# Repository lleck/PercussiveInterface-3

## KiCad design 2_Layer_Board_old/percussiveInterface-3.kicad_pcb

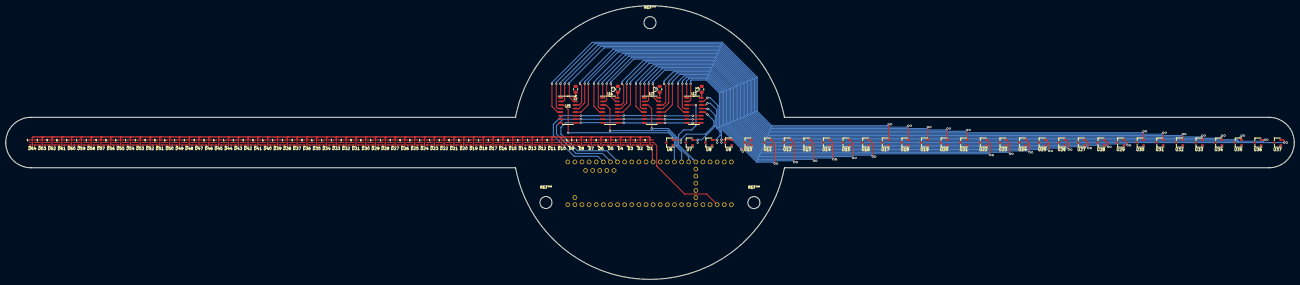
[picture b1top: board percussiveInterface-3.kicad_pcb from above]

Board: 2 copper layers, 460.0 x 97.7 mm, 105 parts (1 on the bottom side), 137 nets.

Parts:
C1, C2, C3, C4: 0.1µF; C_0805_2012Metric_Pad1.18x1.45mm_HandSolder
D1, D2, D3, D4, D5, D6, D7, D8, D9, D10, D11, D12, D13, D14, D15, D16, D17, D18, D19, D20, D21, D22, D23, D24, D25, D26, D27, D28, D29, D30, D31, D32, D33, D34, D35, D36, D37, D38, D39, D40, D41, D42, D43, D44, D45, D46, D47, D48, D49, D50, D51, D52, D53, D54, D55, D56, D57, D58, D59, D60, D61, D62, D63, D64: APA102-2020; LED-APA102-2020
U1: Teensy4.1; TEENSY41
U2, U3, U4, U5: 74HCT4051; SO-16_3.9x9.9mm_P1.27mm
U6, U7, U8, U9, U10, U11, U12, U13, U14, U15, U16, U17, U18, U19, U20, U21, U22, U23, U24, U25, U26, U27, U28, U29, U30, U31, U32, U33, U34, U35, U36, U37: SS39ET; SOT-23W

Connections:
+5V: C1.1, C2.1, C3.1, C4.1, D1.1 (VDD), D2.1 (VDD), D3.1 (VDD), D4.1 (VDD), D5.1 (VDD), D6.1 (VDD), D7.1 (VDD), D8.1 (VDD), D9.1 (VDD), D10.1 (VDD), D11.1 (VDD), D12.1 (VDD), D13.1 (VDD), D14.1 (VDD), D15.1 (VDD), D16.1 (VDD), D17.1 (VDD), D18.1 (VDD), D19.1 (VDD), D20.1 (VDD), D21.1 (VDD), D22.1 (VDD), D23.1 (VDD), D24.1 (VDD), D25.1 (VDD), D26.1 (VDD), D27.1 (VDD), D28.1 (VDD), D29.1 (VDD), D30.1 (VDD), D31.1 (VDD), D32.1 (VDD), D33.1 (VDD), D34.1 (VDD), D35.1 (VDD), D36.1 (VDD), D37.1 (VDD), D38.1 (VDD), D39.1 (VDD), D40.1 (VDD), D41.1 (VDD), D42.1 (VDD), D43.1 (VDD), D44.1 (VDD), D45.1 (VDD), D46.1 (VDD), D47.1 (VDD), D48.1 (VDD), D49.1 (VDD), D50.1 (VDD), D51.1 (VDD), D52.1 (VDD), D53.1 (VDD), D54.1 (VDD), D55.1 (VDD), D56.1 (VDD), D57.1 (VDD), D58.1 (VDD), D59.1 (VDD), D60.1 (VDD), D61.1 (VDD), D62.1 (VDD), D63.1 (VDD), D64.1 (VDD), U1.48 (VIN), U2.16 (VCC), U3.16 (VCC), U4.16 (VCC), U5.16 (VCC), U6.1 (VCC), U7.1 (VCC), U8.1 (VCC), U9.1 (VCC), U10.1 (VCC), U11.1 (VCC), U12.1 (VCC), U13.1 (VCC), U14.1 (VCC), U15.1 (VCC), U16.1 (VCC), U17.1 (VCC), U18.1 (VCC), U19.1 (VCC), U20.1 (VCC), U21.1 (VCC), U22.1 (VCC), U23.1 (VCC), U24.1 (VCC), U25.1 (VCC), U26.1 (VCC), U27.1 (VCC), U28.1 (VCC), U29.1 (VCC), U30.1 (VCC), U31.1 (VCC), U32.1 (VCC), U33.1 (VCC), U34.1 (VCC), U35.1 (VCC), U36.1 (VCC), U37.1 (VCC)
GND: C1.2, C2.2, C3.2, C4.2, D1.6 (GND), D2.6 (GND), D3.6 (GND), D4.6 (GND), D5.6 (GND), D6.6 (GND), D7.6 (GND), D8.6 (GND), D9.6 (GND), D10.6 (GND), D11.6 (GND), D12.6 (GND), D13.6 (GND), D14.6 (GND), D15.6 (GND), D16.6 (GND), D17.6 (GND), D18.6 (GND), D19.6 (GND), D20.6 (GND), D21.6 (GND), D22.6 (GND), D23.6 (GND), D24.6 (GND), D25.6 (GND), D26.6 (GND), D27.6 (GND), D28.6 (GND), D29.6 (GND), D30.6 (GND), D31.6 (GND), D32.6 (GND), D33.6 (GND), D34.6 (GND), D35.6 (GND), D36.6 (GND), D37.6 (GND), D38.6 (GND), D39.6 (GND), D40.6 (GND), D41.6 (GND), D42.6 (GND), D43.6 (GND), D44.6 (GND), D45.6 (GND), D46.6 (GND), D47.6 (GND), D48.6 (GND), D49.6 (GND), D50.6 (GND), D51.6 (GND), D52.6 (GND), D53.6 (GND), D54.6 (GND), D55.6 (GND), D56.6 (GND), D57.6 (GND), D58.6 (GND), D59.6 (GND), D60.6 (GND), D61.6 (GND), D62.6 (GND), D63.6 (GND), D64.6 (GND), U1.1 (GND), U1.34 (GND), U1.52 (GND), U2.6 (~E), U2.7 (VEE), U2.8 (GND), U3.6 (~E), U3.7 (VEE), U3.8 (GND), U4.6 (~E), U4.7 (VEE), U4.8 (GND), U5.6 (~E), U5.7 (VEE), U5.8 (GND), U6.3 (GND), U7.3 (GND), U8.3 (GND), U9.3 (GND), U10.3 (GND), U11.3 (GND), U12.3 (GND), U13.3 (GND), U14.3 (GND), U15.3 (GND), U16.3 (GND), U17.3 (GND), U18.3 (GND), U19.3 (GND), U20.3 (GND), U21.3 (GND), U22.3 (GND), U23.3 (GND), U24.3 (GND), U25.3 (GND), U26.3 (GND), U27.3 (GND), U28.3 (GND), U29.3 (GND), U30.3 (GND), U31.3 (GND), U32.3 (GND), U33.3 (GND), U34.3 (GND), U35.3 (GND), U36.3 (GND), U37.3 (GND)
unnamed: D1.2 (CKO), D2.5 (CKI)
unnamed: D1.3 (SDO), D2.4 (SDI)
unnamed: D1.4 (SDI), U1.11 (9_OUT1C)
unnamed: D1.5 (CKI), U1.35 (13_SCK_LED)
unnamed: D2.2 (CKO), D3.5 (CKI)
unnamed: D2.3 (SDO), D3.4 (SDI)
unnamed: D3.2 (CKO), D4.5 (CKI)
unnamed: D3.3 (SDO), D4.4 (SDI)
unnamed: D4.2 (CKO), D5.5 (CKI)
unnamed: D4.3 (SDO), D5.4 (SDI)
unnamed: D5.2 (CKO), D6.5 (CKI)
unnamed: D5.3 (SDO), D6.4 (SDI)
unnamed: D6.2 (CKO), D7.5 (CKI)
unnamed: D6.3 (SDO), D7.4 (SDI)
unnamed: D7.2 (CKO), D8.5 (CKI)
unnamed: D7.3 (SDO), D8.4 (SDI)
unnamed: D8.2 (CKO), D9.5 (CKI)
unnamed: D8.3 (SDO), D9.4 (SDI)
unnamed: D10.2 (CKO), D11.5 (CKI)
unnamed: D10.3 (SDO), D11.4 (SDI)
unnamed: D9.3 (SDO), D10.4 (SDI)
unnamed: D9.2 (CKO), D10.5 (CKI)
unnamed: D11.2 (CKO), D12.5 (CKI)
unnamed: D11.3 (SDO), D12.4 (SDI)
unnamed: D12.2 (CKO), D13.5 (CKI)
unnamed: D12.3 (SDO), D13.4 (SDI)
unnamed: D13.2 (CKO), D14.5 (CKI)
unnamed: D13.3 (SDO), D14.4 (SDI)
unnamed: D14.2 (CKO), D15.5 (CKI)
unnamed: D14.3 (SDO), D15.4 (SDI)
unnamed: D15.2 (CKO), D16.5 (CKI)
unnamed: D15.3 (SDO), D16.4 (SDI)
unnamed: D16.2 (CKO), D17.5 (CKI)
unnamed: D16.3 (SDO), D17.4 (SDI)
unnamed: D17.2 (CKO), D18.5 (CKI)
unnamed: D17.3 (SDO), D18.4 (SDI)
unnamed: D18.2 (CKO), D19.5 (CKI)
unnamed: D18.3 (SDO), D19.4 (SDI)
unnamed: D19.2 (CKO), D20.5 (CKI)
unnamed: D19.3 (SDO), D20.4 (SDI)
unnamed: D20.2 (CKO), D21.5 (CKI)
unnamed: D20.3 (SDO), D21.4 (SDI)
unnamed: D21.2 (CKO), D22.5 (CKI)
unnamed: D21.3 (SDO), D22.4 (SDI)
unnamed: D22.2 (CKO), D23.5 (CKI)
unnamed: D22.3 (SDO), D23.4 (SDI)
unnamed: D23.2 (CKO), D24.5 (CKI)
unnamed: D23.3 (SDO), D24.4 (SDI)
unnamed: D24.2 (CKO), D25.5 (CKI)
unnamed: D24.3 (SDO), D25.4 (SDI)
unnamed: D25.2 (CKO), D26.5 (CKI)
unnamed: D25.3 (SDO), D26.4 (SDI)
unnamed: D26.2 (CKO), D27.5 (CKI)
unnamed: D26.3 (SDO), D27.4 (SDI)
unnamed: D27.2 (CKO), D28.5 (CKI)
unnamed: D27.3 (SDO), D28.4 (SDI)
unnamed: D28.2 (CKO), D29.5 (CKI)
unnamed: D28.3 (SDO), D29.4 (SDI)
unnamed: D29.2 (CKO), D30.5 (CKI)
unnamed: D29.3 (SDO), D30.4 (SDI)
unnamed: D30.2 (CKO), D31.5 (CKI)
unnamed: D30.3 (SDO), D31.4 (SDI)
unnamed: D31.2 (CKO), D32.5 (CKI)
unnamed: D31.3 (SDO), D32.4 (SDI)
unnamed: D32.2 (CKO), D33.5 (CKI)
unnamed: D32.3 (SDO), D33.4 (SDI)
unnamed: D33.2 (CKO), D34.5 (CKI)
unnamed: D33.3 (SDO), D34.4 (SDI)
unnamed: D34.2 (CKO), D35.5 (CKI)
unnamed: D34.3 (SDO), D35.4 (SDI)
unnamed: D35.2 (CKO), D36.5 (CKI)
unnamed: D35.3 (SDO), D36.4 (SDI)
unnamed: D36.2 (CKO), D37.5 (CKI)
unnamed: D36.3 (SDO), D37.4 (SDI)
unnamed: D37.2 (CKO), D38.5 (CKI)
unnamed: D37.3 (SDO), D38.4 (SDI)
unnamed: D38.2 (CKO), D39.5 (CKI)
unnamed: D38.3 (SDO), D39.4 (SDI)
unnamed: D39.2 (CKO), D40.5 (CKI)
unnamed: D39.3 (SDO), D40.4 (SDI)
unnamed: D40.2 (CKO), D41.5 (CKI)
unnamed: D40.3 (SDO), D41.4 (SDI)
unnamed: D41.2 (CKO), D42.5 (CKI)
unnamed: D41.3 (SDO), D42.4 (SDI)
unnamed: D42.2 (CKO), D43.5 (CKI)
unnamed: D42.3 (SDO), D43.4 (SDI)
unnamed: D43.2 (CKO), D44.5 (CKI)
unnamed: D43.3 (SDO), D44.4 (SDI)
unnamed: D44.2 (CKO), D45.5 (CKI)
unnamed: D44.3 (SDO), D45.4 (SDI)
unnamed: D45.2 (CKO), D46.5 (CKI)
unnamed: D45.3 (SDO), D46.4 (SDI)
unnamed: D46.2 (CKO), D47.5 (CKI)
unnamed: D46.3 (SDO), D47.4 (SDI)
unnamed: D47.2 (CKO), D48.5 (CKI)
unnamed: D47.3 (SDO), D48.4 (SDI)
unnamed: D48.2 (CKO), D49.5 (CKI)
unnamed: D48.3 (SDO), D49.4 (SDI)
unnamed: D49.2 (CKO), D50.5 (CKI)
unnamed: D49.3 (SDO), D50.4 (SDI)
unnamed: D50.2 (CKO), D51.5 (CKI)
unnamed: D50.3 (SDO), D51.4 (SDI)
unnamed: D51.2 (CKO), D52.5 (CKI)
unnamed: D51.3 (SDO), D52.4 (SDI)
unnamed: D52.2 (CKO), D53.5 (CKI)
unnamed: D52.3 (SDO), D53.4 (SDI)
unnamed: D53.2 (CKO), D54.5 (CKI)
unnamed: D53.3 (SDO), D54.4 (SDI)
unnamed: D54.2 (CKO), D55.5 (CKI)
unnamed: D54.3 (SDO), D55.4 (SDI)
unnamed: D55.2 (CKO), D56.5 (CKI)
unnamed: D55.3 (SDO), D56.4 (SDI)
unnamed: D56.2 (CKO), D57.5 (CKI)
unnamed: D56.3 (SDO), D57.4 (SDI)
unnamed: D57.2 (CKO), D58.5 (CKI)
unnamed: D57.3 (SDO), D58.4 (SDI)
unnamed: D58.2 (CKO), D59.5 (CKI)
unnamed: D58.3 (SDO), D59.4 (SDI)
unnamed: D59.2 (CKO), D60.5 (CKI)
unnamed: D59.3 (SDO), D60.4 (SDI)
unnamed: D60.2 (CKO), D61.5 (CKI)
unnamed: D60.3 (SDO), D61.4 (SDI)
unnamed: D61.2 (CKO), D62.5 (CKI)
unnamed: D61.3 (SDO), D62.4 (SDI)
unnamed: D62.2 (CKO), D63.5 (CKI)
unnamed: D62.3 (SDO), D63.4 (SDI)
unnamed: D63.2 (CKO), D64.5 (CKI)
unnamed: D63.3 (SDO), D64.4 (SDI)
unnamed: U1.27 (35_TX8), U2.3 (A)
unnamed: U1.6 (4_BCLK2), U2.9 (S2), U3.9 (S2), U4.9 (S2), U5.9 (S2)
unnamed: U1.5 (3_LRCLK2), U2.10 (S1), U3.10 (S1), U4.10 (S1), U5.10 (S1)
unnamed: U1.4 (2_OUT2), U2.11 (S0), U3.11 (S0), U4.11 (S0), U5.11 (S0)
unnamed: U1.26 (34_RX8), U3.3 (A)
unnamed: U1.25 (33_MCLK2), U4.3 (A)
unnamed: U1.24 (32_OUT1B), U5.3 (A)
